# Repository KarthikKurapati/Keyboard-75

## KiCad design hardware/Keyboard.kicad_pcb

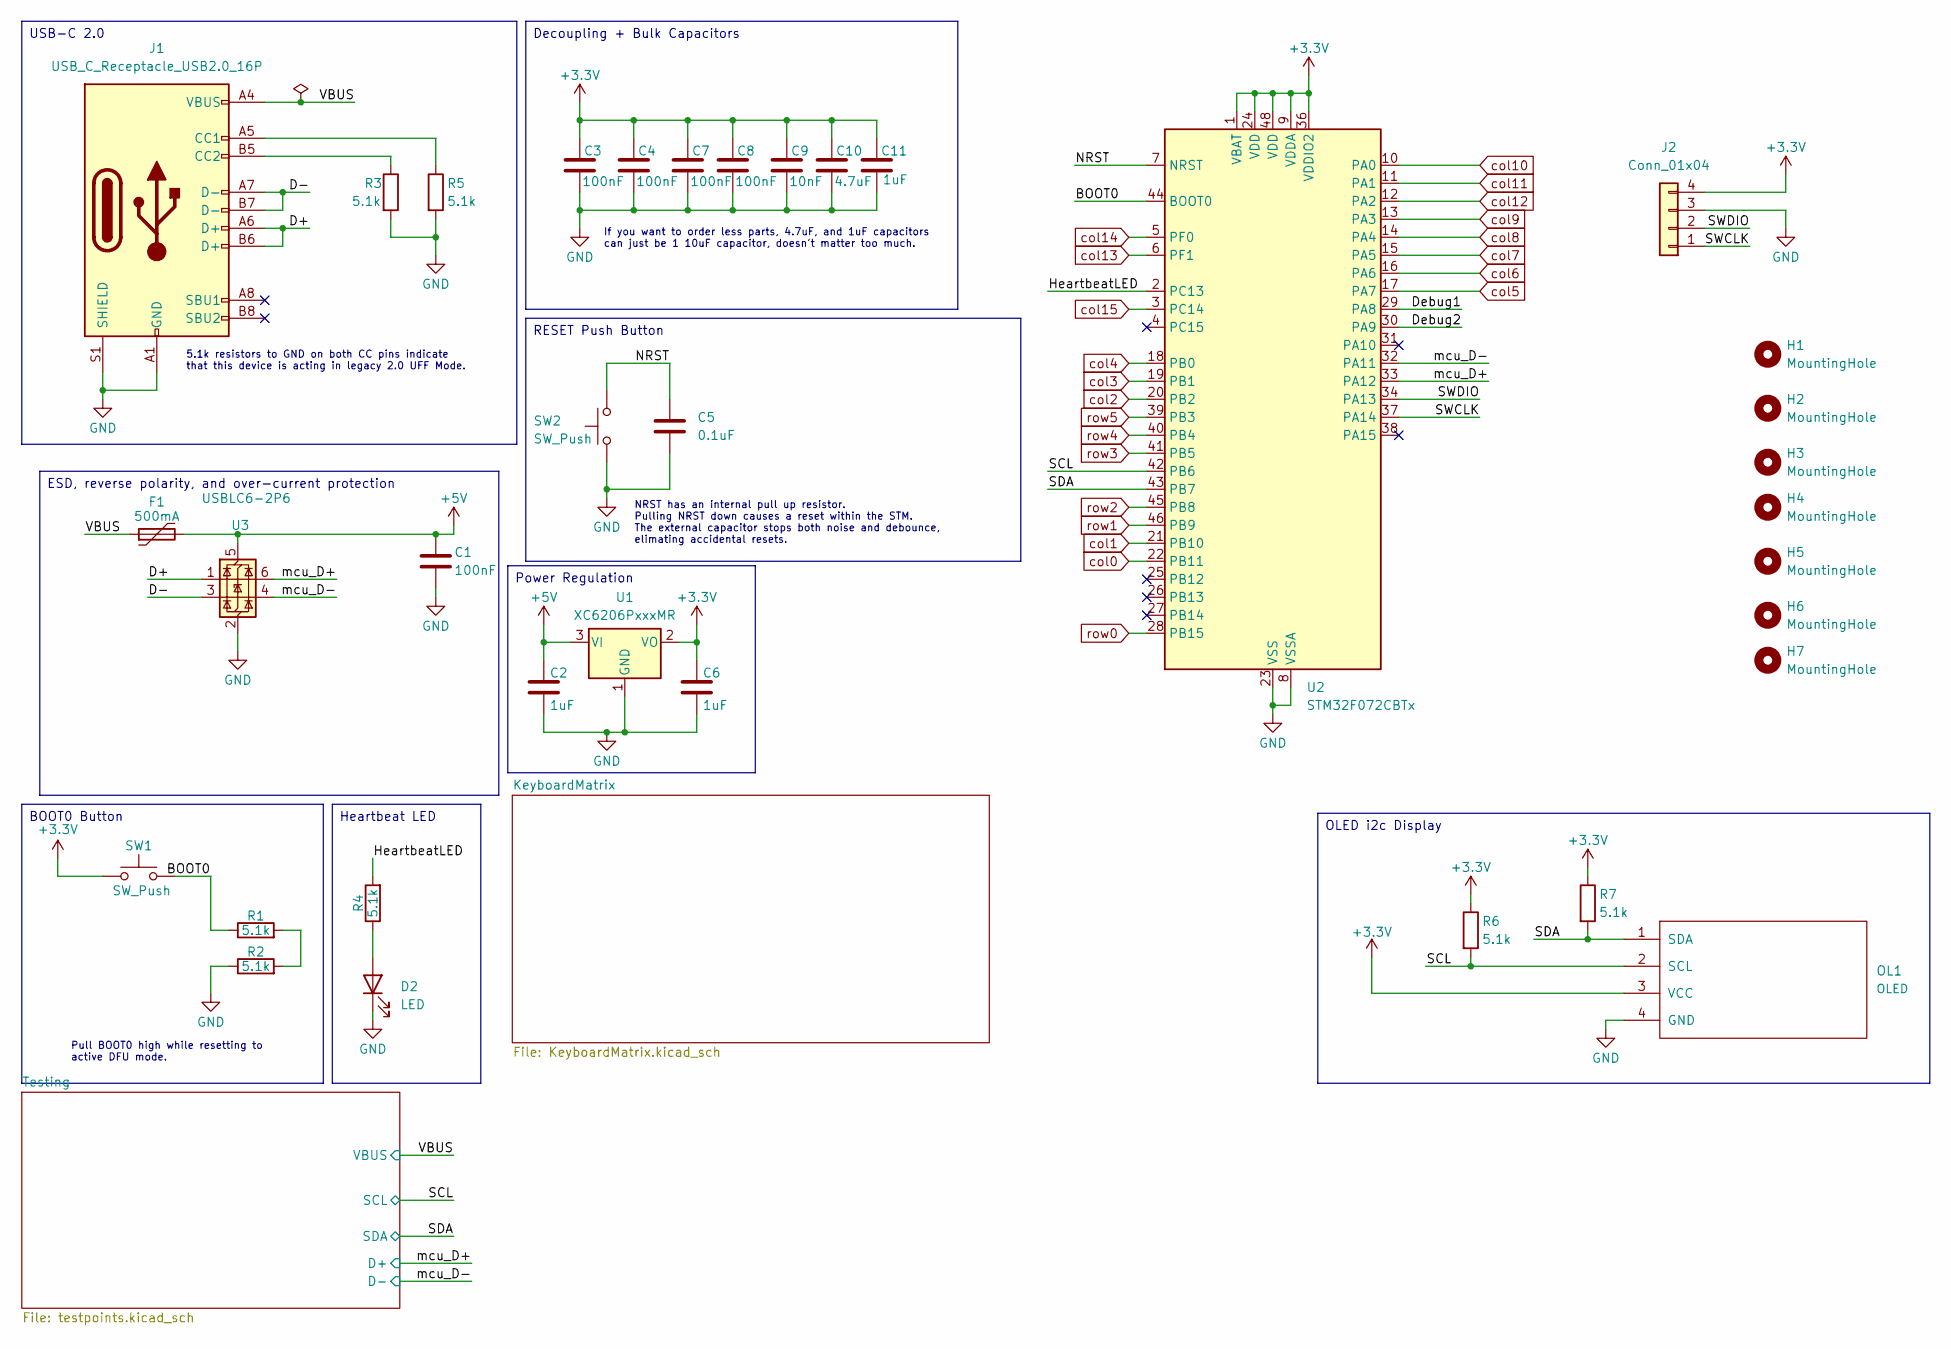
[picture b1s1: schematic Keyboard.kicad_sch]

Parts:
C1, C3, C4, C7, C8: 100nF; C_0603_1608Metric_Pad1.08x0.95mm_HandSolder
C2, C6, C11: 1uF; C_0603_1608Metric_Pad1.08x0.95mm_HandSolder
C5: 0.1uF; C_0603_1608Metric_Pad1.08x0.95mm_HandSolder
C9: 10nF; C_0603_1608Metric_Pad1.08x0.95mm_HandSolder
C10: 4.7uF; C_0603_1608Metric_Pad1.08x0.95mm_HandSolder
D2: LED; LED_0603_1608Metric_Pad1.05x0.95mm_HandSolder
F1: 500mA; Fuse_0603_1608Metric
H1, H2, H3, H4, H5, H6, H7: MountingHole; MountingHole_3.2mm_M3_ISO7380
J1: USB_C_Receptacle_USB2.0_16P; USB_C_Receptacle_GCT_USB4105-xx-A_16P_TopMnt_Horizontal
J2: Conn_01x04; PinHeader_1x04_P2.54mm_Vertical
OL1: OLED
R1, R2, R3, R4, R5, R6, R7: 5.1k; R_0603_1608Metric_Pad0.98x0.95mm_HandSolder
SW1, SW2: SW_Push; SW_Push_SPST_NO_Alps_SKRK
U1: XC6206PxxxMR; SOT-23-3
U2: STM32F072CBTx; LQFP-48_7x7mm_P0.5mm
U3: USBLC6-2P6; SOT-666

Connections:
+3.3V: C3.1, C4.1, C6.1, C7.1, C8.1, C9.1, C10.1, C11.1, J2.4, OL1.3 (VCC), R6.1, R7.1, SW1.1, U1.2 (VO), U2.1 (VBAT), U2.9 (VDDA), U2.24 (VDD), U2.36 (VDDIO2), U2.48 (VDD); also elsewhere on the board
+5V: C1.1, C2.1, F1.2, U1.3 (VI), U3.5 (VBUS); also elsewhere on the board
/BOOT0: R1.1, SW1.2, U2.44 (BOOT0)
/D+: J1.A6 (D+), J1.B6 (D+), U3.1 (I/O1)
/D-: J1.A7 (D-), J1.B7 (D-), U3.3 (I/O2)
/Debug1: U2.29 (PA8)
/Debug2: U2.30 (PA9)
/HeartbeatLED: R4.2, U2.2 (PC13)
/NRST: C5.1, SW2.2, U2.7 (NRST)
/SCL: OL1.2 (SCL), R6.2, U2.42 (PB6); also elsewhere on the board
/SDA: OL1.1 (SDA), R7.2, U2.43 (PB7); also elsewhere on the board
/SWCLK: J2.1, U2.37 (PA14)
/SWDIO: J2.2, U2.34 (PA13)
/VBUS: F1.1, J1.A4 (VBUS), J1.A9 (VBUS), J1.B4 (VBUS), J1.B9 (VBUS); also elsewhere on the board
/mcu_D+: U2.33 (PA12), U3.6 (I/O1); also elsewhere on the board
/mcu_D-: U2.32 (PA11), U3.4 (I/O2); also elsewhere on the board
GND: C1.2, C2.2, C3.2, C4.2, C5.2, C6.2, C7.2, C8.2, C9.2, C10.2, C11.2, D2.1 (K), J1.A1 (GND), J1.A12 (GND), J1.B1 (GND), J1.B12 (GND), J1.S1 (SHIELD), J2.3, OL1.4 (GND), R2.1, R3.2, R5.2, SW2.1, U1.1 (GND), U2.8 (VSSA), U2.23 (VSS), U2.35 (VSS), U2.47 (VSS), U3.2 (GND); also elsewhere on the board
unnamed: D2.2 (A), R4.1
unnamed: J1.A5 (CC1), R5.1
unnamed: J1.B5 (CC2), R3.1
unnamed: R1.2, R2.2
col0: U2.22 (PB11); also elsewhere on the board
col1: U2.21 (PB10); also elsewhere on the board
col2: U2.20 (PB2); also elsewhere on the board
col3: U2.19 (PB1); also elsewhere on the board
col4: U2.18 (PB0); also elsewhere on the board
col5: U2.17 (PA7); also elsewhere on the board
col6: U2.16 (PA6); also elsewhere on the board
col7: U2.15 (PA5); also elsewhere on the board
col8: U2.14 (PA4); also elsewhere on the board
col9: U2.13 (PA3); also elsewhere on the board
col10: U2.10 (PA0); also elsewhere on the board
col11: U2.11 (PA1); also elsewhere on the board
col12: U2.12 (PA2); also elsewhere on the board
col13: U2.6 (PF1); also elsewhere on the board
col14: U2.5 (PF0); also elsewhere on the board
col15: U2.3 (PC14); also elsewhere on the board
row0: U2.28 (PB15); also elsewhere on the board
row1: U2.46 (PB9); also elsewhere on the board
row2: U2.45 (PB8); also elsewhere on the board
row3: U2.41 (PB5); also elsewhere on the board
row4: U2.40 (PB4); also elsewhere on the board
row5: U2.39 (PB3); also elsewhere on the board

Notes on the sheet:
NRST has an internal pull up resistor. Pulling NRST down causes a reset within the STM. The external capacitor stops both noise and debounce, elimating accidental resets.
5.1k resistors to GND on both CC pins indicate that this device is acting in legacy 2.0 UFF Mode.
If you want to order less parts, 4.7uF, and 1uF capacitors can just be 1 10uF capacitor, doesn't matter too much.
Pull BOOT0 high while resetting to active DFU mode.
RESET Push Button
OLED i2c Display
ESD, reverse polarity, and over-current protection
BOOT0 Button
Power Regulation
Heartbeat LED
Decoupling + Bulk Capacitors
USB-C 2.0

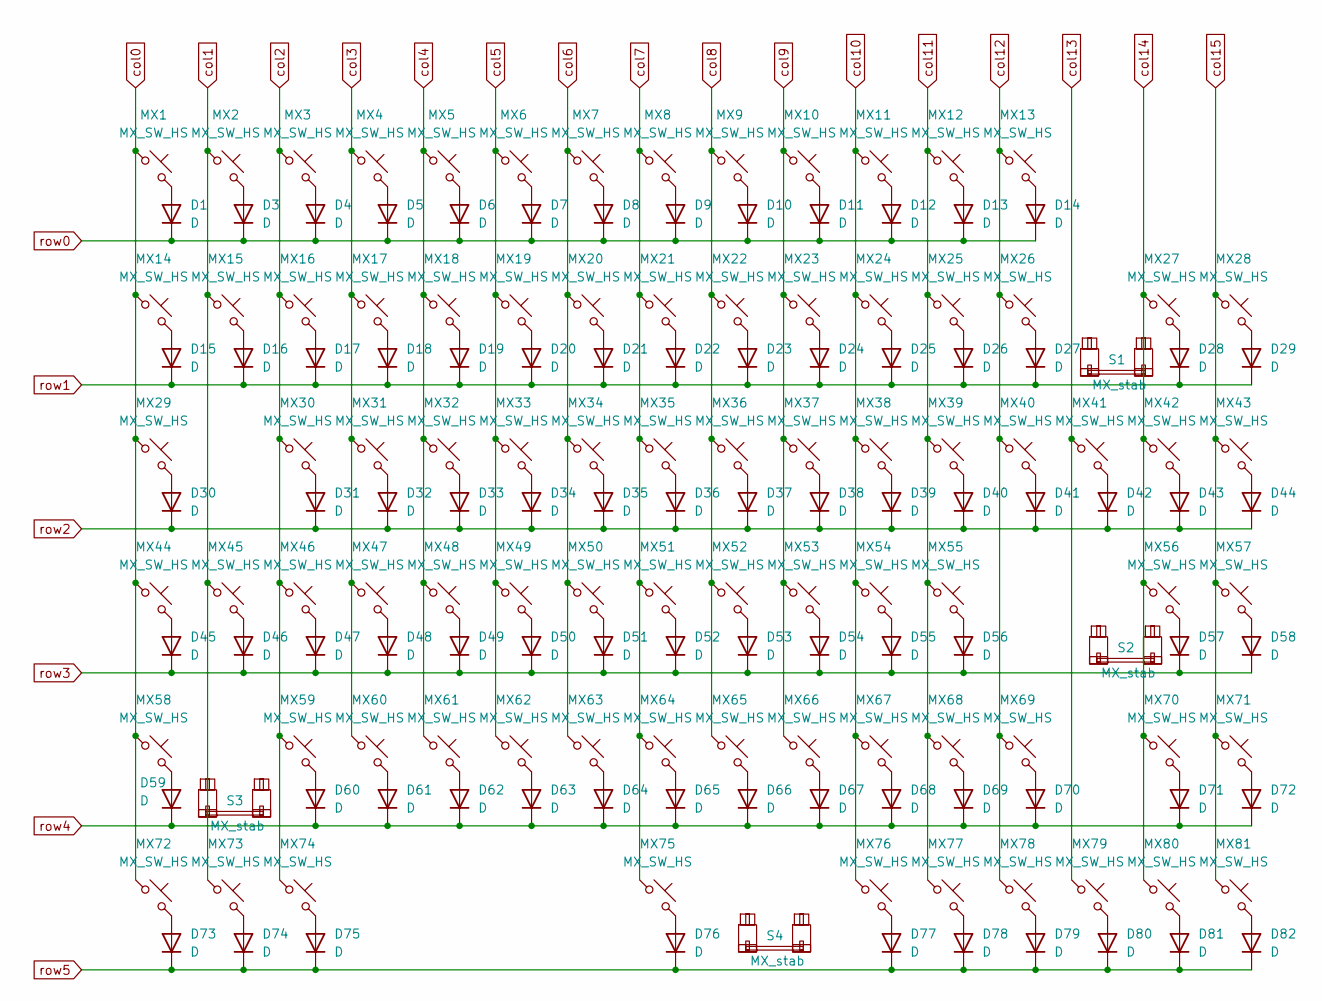
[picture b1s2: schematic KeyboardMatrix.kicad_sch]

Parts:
D1, D3, D4, D5, D6, D7, D8, D9, D10, D11, D12, D13, D14, D15, D16, D17, D18, D19, D20, D21, D22, D23, D24, D25, D26, D27, D28, D29, D30, D31, D32, D33, D34, D35, D36, D37, D38, D39, D40, D41, D42, D43, D44, D45, D46, D47, D48, D49, D50, D51, D52, D53, D54, D55, D56, D57, D58, D59, D60, D61, D62, D63, D64, D65, D66, D67, D68, D69, D70, D71, D72, D73, D74, D75, D76, D77, D78, D79, D80, D81, D82: D; D_SOD-123
MX1, MX2, MX3, MX4, MX5, MX6, MX7, MX8, MX9, MX10, MX11, MX12, MX13, MX14, MX15, MX16, MX17, MX18, MX19, MX20, MX21, MX22, MX23, MX24, MX25, MX26, MX27, MX28, MX29, MX30, MX31, MX32, MX33, MX34, MX35, MX36, MX37, MX38, MX39, MX40, MX41, MX42, MX43, MX44, MX45, MX46, MX47, MX48, MX49, MX50, MX51, MX52, MX53, MX54, MX55, MX56, MX57, MX58, MX59, MX60, MX61, MX62, MX63, MX64, MX65, MX66, MX67, MX68, MX69, MX70, MX71, MX72, MX73, MX74, MX75, MX76, MX77, MX78, MX79, MX80, MX81: MX_SW_HS; SW_MX_HS_CPG151101S11_1u
S1, S2, S3: MX_stab; STAB_MX_P_2u
S4: MX_stab; STAB_MX_P_6.25u

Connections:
unnamed: D1.2 (A), MX1.2
unnamed: D3.2 (A), MX2.2
unnamed: D4.2 (A), MX3.2
unnamed: D5.2 (A), MX4.2
unnamed: D6.2 (A), MX5.2
unnamed: D7.2 (A), MX6.2
unnamed: D8.2 (A), MX7.2
unnamed: D9.2 (A), MX8.2
unnamed: D10.2 (A), MX9.2
unnamed: D11.2 (A), MX10.2
unnamed: D12.2 (A), MX11.2
unnamed: D13.2 (A), MX12.2
unnamed: D14.2 (A), MX13.2
unnamed: D15.2 (A), MX14.2
unnamed: D16.2 (A), MX15.2
unnamed: D17.2 (A), MX16.2
unnamed: D18.2 (A), MX17.2
unnamed: D19.2 (A), MX18.2
unnamed: D20.2 (A), MX19.2
unnamed: D21.2 (A), MX20.2
unnamed: D22.2 (A), MX21.2
unnamed: D23.2 (A), MX22.2
unnamed: D24.2 (A), MX23.2
unnamed: D25.2 (A), MX24.2
unnamed: D26.2 (A), MX25.2
unnamed: D27.2 (A), MX26.2
unnamed: D28.2 (A), MX27.2
unnamed: D29.2 (A), MX28.2
unnamed: D30.2 (A), MX29.2
unnamed: D31.2 (A), MX30.2
unnamed: D32.2 (A), MX31.2
unnamed: D33.2 (A), MX32.2
unnamed: D34.2 (A), MX33.2
unnamed: D35.2 (A), MX34.2
unnamed: D36.2 (A), MX35.2
unnamed: D37.2 (A), MX36.2
unnamed: D38.2 (A), MX37.2
unnamed: D39.2 (A), MX38.2
unnamed: D40.2 (A), MX39.2
unnamed: D41.2 (A), MX40.2
unnamed: D42.2 (A), MX41.2
unnamed: D43.2 (A), MX42.2
unnamed: D44.2 (A), MX43.2
unnamed: D45.2 (A), MX44.2
unnamed: D46.2 (A), MX45.2
unnamed: D47.2 (A), MX46.2
unnamed: D48.2 (A), MX47.2
unnamed: D49.2 (A), MX48.2
unnamed: D50.2 (A), MX49.2
unnamed: D51.2 (A), MX50.2
unnamed: D52.2 (A), MX51.2
unnamed: D53.2 (A), MX52.2
unnamed: D54.2 (A), MX53.2
unnamed: D55.2 (A), MX54.2
unnamed: D56.2 (A), MX55.2
unnamed: D57.2 (A), MX56.2
unnamed: D58.2 (A), MX57.2
unnamed: D59.2 (A), MX58.2
unnamed: D60.2 (A), MX59.2
unnamed: D61.2 (A), MX60.2
unnamed: D62.2 (A), MX61.2
unnamed: D63.2 (A), MX62.2
unnamed: D64.2 (A), MX63.2
unnamed: D65.2 (A), MX64.2
unnamed: D66.2 (A), MX65.2
unnamed: D67.2 (A), MX66.2
unnamed: D68.2 (A), MX67.2
unnamed: D69.2 (A), MX68.2
unnamed: D70.2 (A), MX69.2
unnamed: D71.2 (A), MX70.2
unnamed: D72.2 (A), MX71.2
unnamed: D73.2 (A), MX72.2
unnamed: D74.2 (A), MX73.2
unnamed: D75.2 (A), MX74.2
unnamed: D76.2 (A), MX75.2
unnamed: D77.2 (A), MX76.2
unnamed: D78.2 (A), MX77.2
unnamed: D79.2 (A), MX78.2
unnamed: D80.2 (A), MX79.2
unnamed: D81.2 (A), MX80.2
unnamed: D82.2 (A), MX81.2
col0: MX1.1, MX14.1, MX29.1, MX44.1, MX58.1, MX72.1; also elsewhere on the board
col1: MX2.1, MX15.1, MX45.1, MX73.1; also elsewhere on the board
col2: MX3.1, MX16.1, MX30.1, MX46.1, MX59.1, MX74.1; also elsewhere on the board
col3: MX4.1, MX17.1, MX31.1, MX47.1, MX60.1; also elsewhere on the board
col4: MX5.1, MX18.1, MX32.1, MX48.1, MX61.1; also elsewhere on the board
col5: MX6.1, MX19.1, MX33.1, MX49.1, MX62.1; also elsewhere on the board
col6: MX7.1, MX20.1, MX34.1, MX50.1, MX63.1; also elsewhere on the board
col7: MX8.1, MX21.1, MX35.1, MX51.1, MX64.1, MX75.1; also elsewhere on the board
col8: MX9.1, MX22.1, MX36.1, MX52.1, MX65.1; also elsewhere on the board
col9: MX10.1, MX23.1, MX37.1, MX53.1, MX66.1; also elsewhere on the board
col10: MX11.1, MX24.1, MX38.1, MX54.1, MX67.1, MX76.1; also elsewhere on the board
col11: MX12.1, MX25.1, MX39.1, MX55.1, MX68.1, MX77.1; also elsewhere on the board
col12: MX13.1, MX26.1, MX40.1, MX69.1, MX78.1; also elsewhere on the board
col13: MX41.1, MX79.1; also elsewhere on the board
col14: MX27.1, MX42.1, MX56.1, MX70.1, MX80.1; also elsewhere on the board
col15: MX28.1, MX43.1, MX57.1, MX71.1, MX81.1; also elsewhere on the board
row0: D1.1 (K), D3.1 (K), D4.1 (K), D5.1 (K), D6.1 (K), D7.1 (K), D8.1 (K), D9.1 (K), D10.1 (K), D11.1 (K), D12.1 (K), D13.1 (K), D14.1 (K); also elsewhere on the board
row1: D15.1 (K), D16.1 (K), D17.1 (K), D18.1 (K), D19.1 (K), D20.1 (K), D21.1 (K), D22.1 (K), D23.1 (K), D24.1 (K), D25.1 (K), D26.1 (K), D27.1 (K), D28.1 (K), D29.1 (K); also elsewhere on the board
row2: D30.1 (K), D31.1 (K), D32.1 (K), D33.1 (K), D34.1 (K), D35.1 (K), D36.1 (K), D37.1 (K), D38.1 (K), D39.1 (K), D40.1 (K), D41.1 (K), D42.1 (K), D43.1 (K), D44.1 (K); also elsewhere on the board
row3: D45.1 (K), D46.1 (K), D47.1 (K), D48.1 (K), D49.1 (K), D50.1 (K), D51.1 (K), D52.1 (K), D53.1 (K), D54.1 (K), D55.1 (K), D56.1 (K), D57.1 (K), D58.1 (K); also elsewhere on the board
row4: D59.1 (K), D60.1 (K), D61.1 (K), D62.1 (K), D63.1 (K), D64.1 (K), D65.1 (K), D66.1 (K), D67.1 (K), D68.1 (K), D69.1 (K), D70.1 (K), D71.1 (K), D72.1 (K); also elsewhere on the board
row5: D73.1 (K), D74.1 (K), D75.1 (K), D76.1 (K), D77.1 (K), D78.1 (K), D79.1 (K), D80.1 (K), D81.1 (K), D82.1 (K); also elsewhere on the board

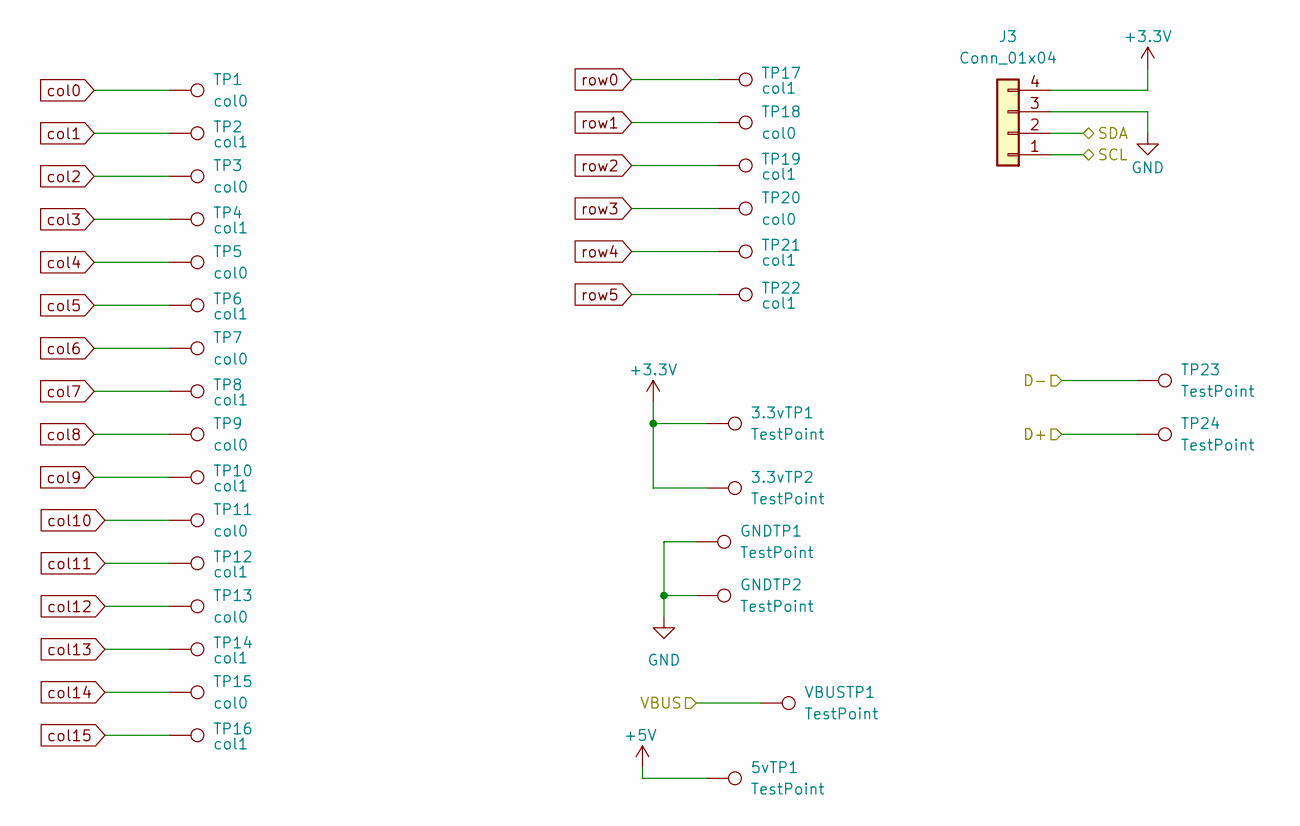
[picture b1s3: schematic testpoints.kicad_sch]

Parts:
3.3vTP1, 3.3vTP2, 5vTP1: TestPoint; TestPoint_Pad_2.0x2.0mm
GNDTP1, GNDTP2: TestPoint; TestPoint_Pad_2.0x2.0mm
J3: Conn_01x04; PinHeader_1x04_P2.54mm_Vertical
TP1, TP3, TP5, TP7, TP9, TP11, TP13, TP15, TP18, TP20: col0; TestPoint_Pad_2.0x2.0mm
TP2, TP4, TP6, TP8, TP10, TP12, TP14, TP16, TP17, TP19, TP21, TP22: col1; TestPoint_Pad_2.0x2.0mm
TP23, TP24: TestPoint; TestPoint_THTPad_1.0x1.0mm_Drill0.5mm
VBUSTP1: TestPoint; TestPoint_Pad_2.0x2.0mm

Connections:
+3.3V: 3.3vTP1.1, 3.3vTP2.1, J3.4; also elsewhere on the board
+5V: 5vTP1.1; also elsewhere on the board
/SCL: J3.1; also elsewhere on the board
/SDA: J3.2; also elsewhere on the board
/VBUS: VBUSTP1.1; also elsewhere on the board
/mcu_D+: TP24.1; also elsewhere on the board
/mcu_D-: TP23.1; also elsewhere on the board
GND: GNDTP1.1, GNDTP2.1, J3.3; also elsewhere on the board
col0: TP1.1; also elsewhere on the board
col1: TP2.1; also elsewhere on the board
col2: TP3.1; also elsewhere on the board
col3: TP4.1; also elsewhere on the board
col4: TP5.1; also elsewhere on the board
col5: TP6.1; also elsewhere on the board
col6: TP7.1; also elsewhere on the board
col7: TP8.1; also elsewhere on the board
col8: TP9.1; also elsewhere on the board
col9: TP10.1; also elsewhere on the board
col10: TP11.1; also elsewhere on the board
col11: TP12.1; also elsewhere on the board
col12: TP13.1; also elsewhere on the board
col13: TP14.1; also elsewhere on the board
col14: TP15.1; also elsewhere on the board
col15: TP16.1; also elsewhere on the board
row0: TP17.1; also elsewhere on the board
row1: TP18.1; also elsewhere on the board
row2: TP19.1; also elsewhere on the board
row3: TP20.1; also elsewhere on the board
row4: TP21.1; also elsewhere on the board
row5: TP22.1; also elsewhere on the board

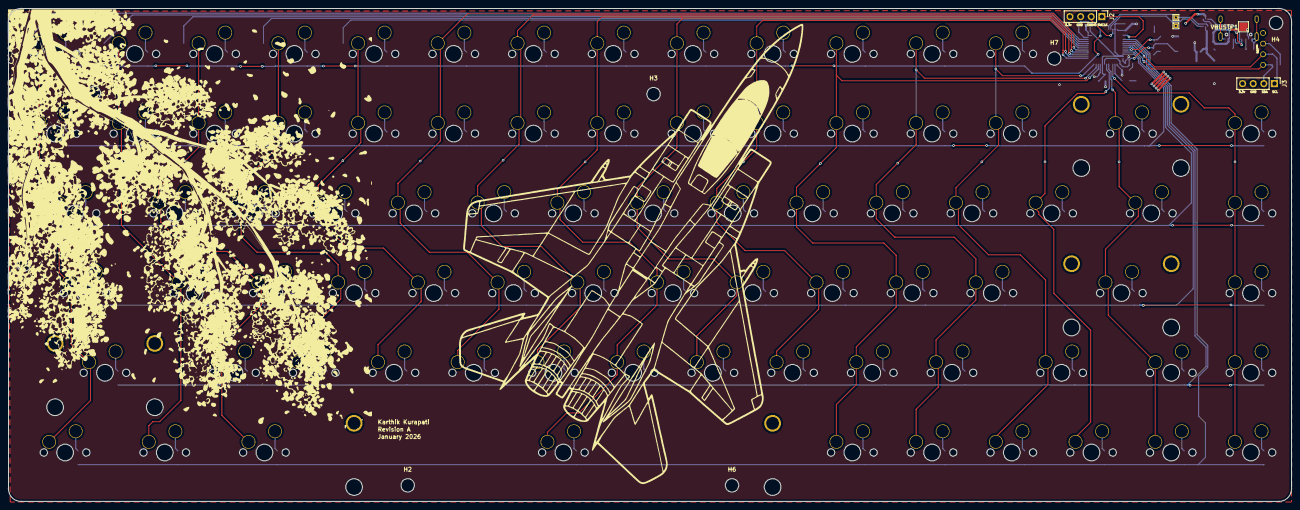
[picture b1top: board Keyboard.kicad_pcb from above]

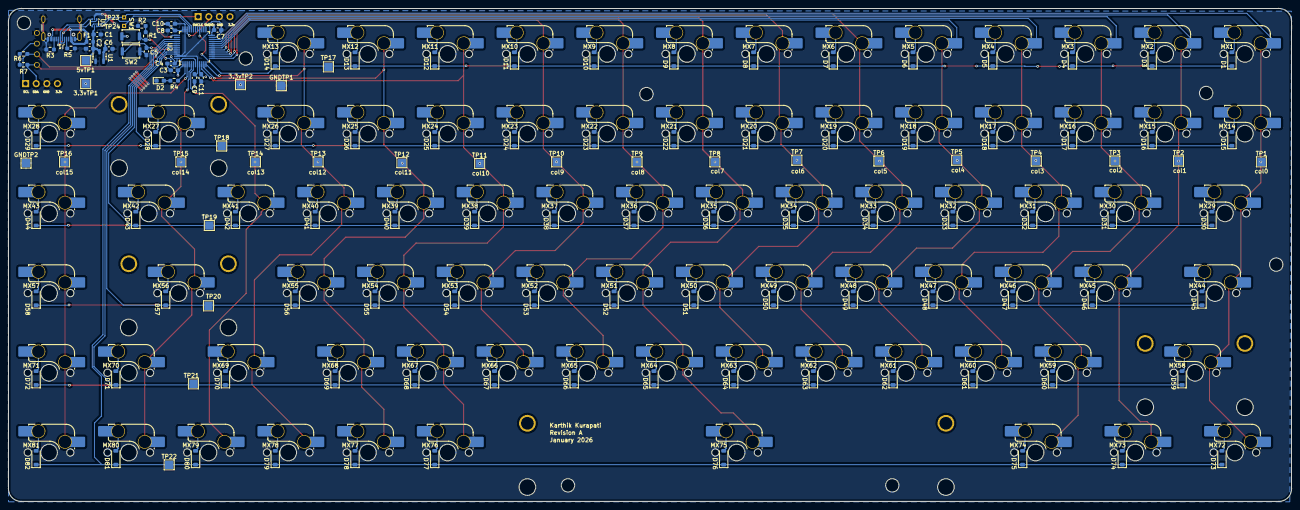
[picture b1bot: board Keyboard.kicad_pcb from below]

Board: 2 copper layers, 306.6 x 117.8 mm, 232 parts (215 on the bottom side), 122 nets.

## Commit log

2025-12-25 inital commit
2025-12-26 stm32layout done, started routing board
2025-12-26 finished routing --> need to add test points and add i2c display. also need to request a review and refine routing.
2025-12-29 added OLED display + new libary for it
    things to add:
    test points
    3.3v, 5v LED
    fix some wiring
2025-12-30 added testpoints, need to readd library
2025-12-30 ready for review!
2026-01-09 production files added --> ready for assembly
